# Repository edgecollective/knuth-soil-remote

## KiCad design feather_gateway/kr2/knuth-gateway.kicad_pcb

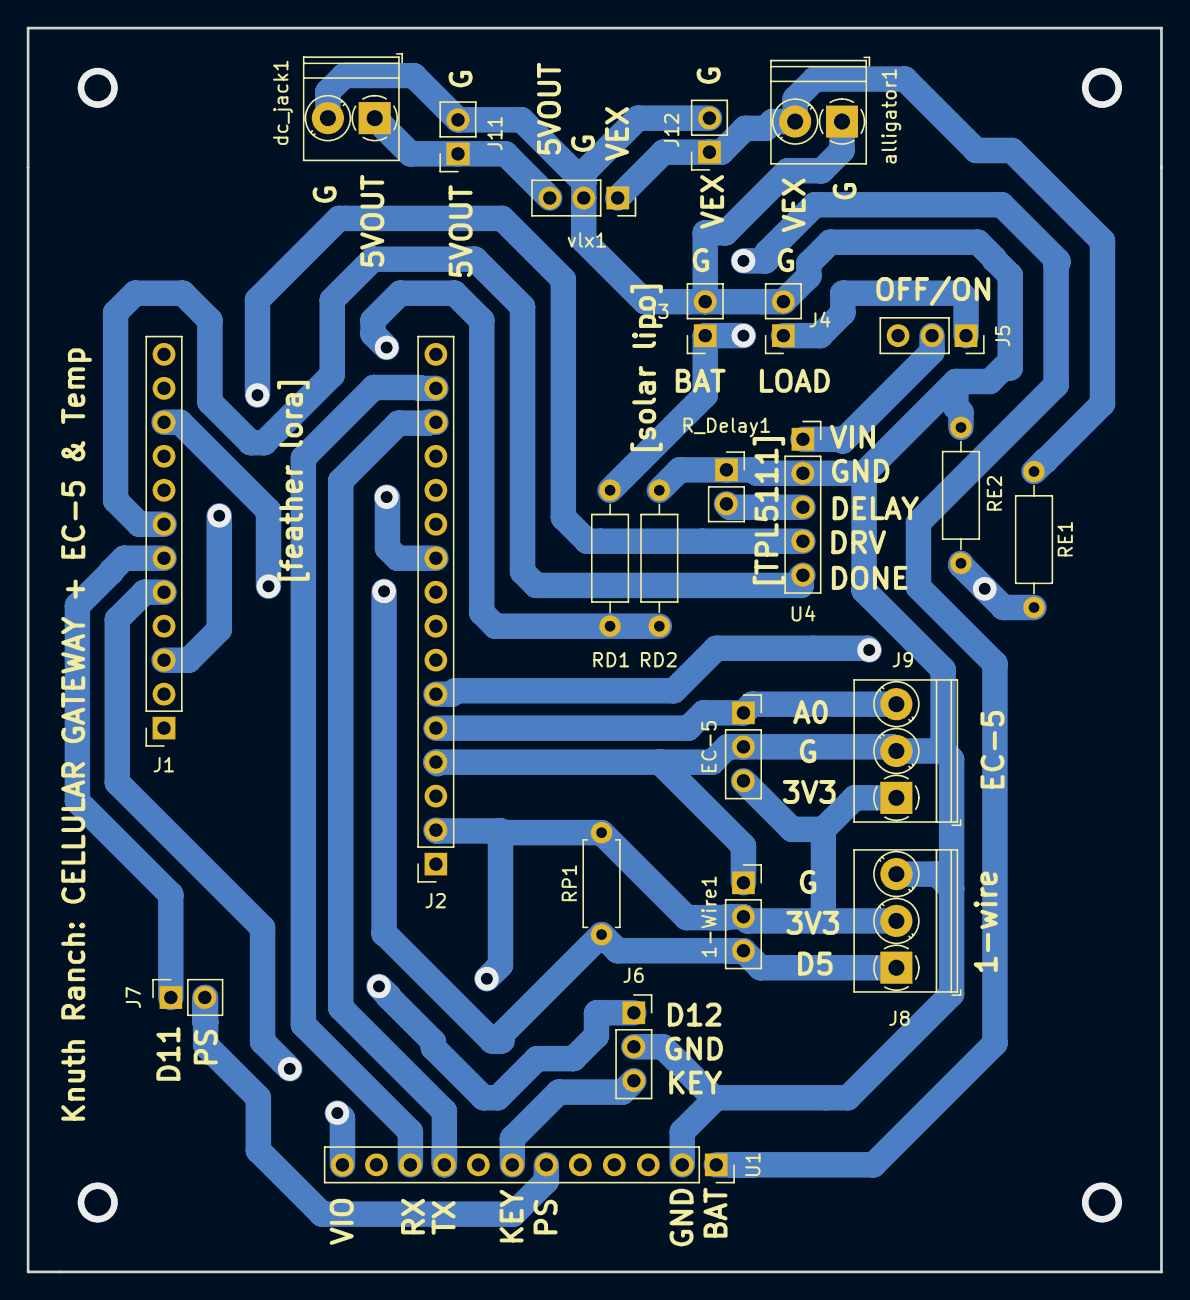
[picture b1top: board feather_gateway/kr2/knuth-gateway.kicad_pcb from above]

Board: 2 copper layers, 84.7 x 93.0 mm, 24 parts (0 on the bottom side), 20 nets.

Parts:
1-Wire1: Conn_01x03_Female; PinSocket_1x03_P2.54mm_Vertical
EC-5: Conn_01x03_Female; PinSocket_1x03_P2.54mm_Vertical
J1: FeatherLora1; PinSocket_1x12_P2.54mm_Vertical
J2: FeatherLora2; PinSocket_1x16_P2.54mm_Vertical
J3, J4, J7, J11, J12: Conn_01x02_Female; PinSocket_1x02_P2.54mm_Vertical
J5, J6: Conn_01x03_Female; PinSocket_1x03_P2.54mm_Vertical
J8, J9: Screw_Terminal_01x03; TerminalBlock_Phoenix_PT-1,5-3-3.5-H_1x03_P3.50mm_Horizontal
RD1, RD2: R; R_Axial_DIN0207_L6.3mm_D2.5mm_P10.16mm_Horizontal
RE1: R; R_Axial_DIN0207_L6.3mm_D2.5mm_P10.16mm_Horizontal
RE2: =1/14 of top R; R_Axial_DIN0207_L6.3mm_D2.5mm_P10.16mm_Horizontal
RP1: 4.7K; R_Axial_DIN0207_L6.3mm_D2.5mm_P7.62mm_Horizontal
R_Delay1: Conn_01x02_Female; PinSocket_1x02_P2.54mm_Vertical
U1: sim800; PinSocket_1x12_P2.54mm_Vertical
U4: tpl5111; PinSocket_1x05_P2.54mm_Vertical
alligator1: Screw_Terminal_01x02; TerminalBlock_Phoenix_PT-1,5-2-3.5-H_1x02_P3.50mm_Horizontal
dc_jack1: Screw_Terminal_01x02; TerminalBlock_Phoenix_PT-1,5-2-3.5-H_1x02_P3.50mm_Horizontal
vlx1: Conn_01x03_Female; PinSocket_1x03_P2.54mm_Vertical

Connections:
5V_OUT: J11.1, dc_jack1.1, vlx1.3
+3V3: 1-Wire1.2, EC-5.3, J2.2, J8.2, J9.1, RP1.2, U1.12
A0: EC-5.1, J2.5, J9.3
A1: J2.6, RE1.2, RE2.1
A5: J2.10, RD1.2, RD2.1
BATT: J3.1, RD1.1, U1.1
D5: 1-Wire1.3, J1.10, J8.1, RP1.1
D10: J1.7, U4.5
D11: J1.6, J7.1
D12: J1.5, J6.1
EXT_BAT: J12.1, RE1.1, alligator1.2, vlx1.1
FEATHER_RX: J2.14, U1.9
FEATHER_TX: J2.15, U1.10
GND: 1-Wire1.1, EC-5.2, J2.4, J3.2, J4.2, J6.2, J8.3, J9.2, J11.2, J12.2, RD2.2, RE2.2, R_Delay1.1, U1.2, U4.2, alligator1.1, dc_jack1.2, vlx1.2
KEY: J6.3, U1.7
LOAD: J4.1, J5.1
unnamed: R_Delay1.2, U4.3
PS: J7.2, U1.6
SWITCHED_LOAD: J5.2, U4.1
VBUS: J1.3, U4.4

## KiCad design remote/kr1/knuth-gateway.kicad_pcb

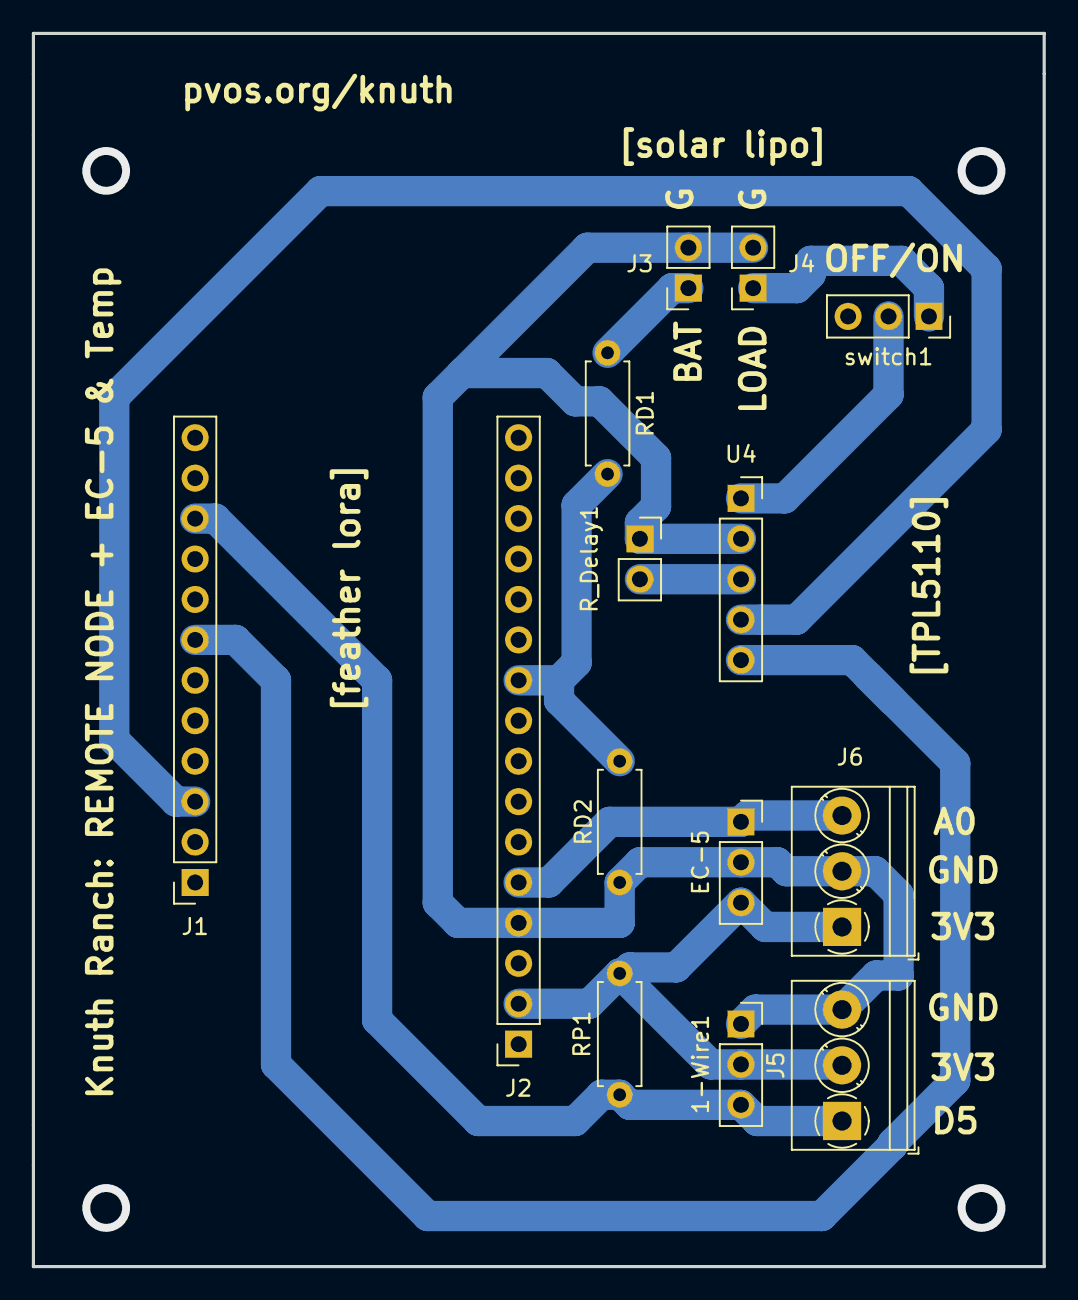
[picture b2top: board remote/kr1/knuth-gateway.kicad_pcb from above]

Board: 2 copper layers, 63.5 x 77.5 mm, 14 parts (0 on the bottom side), 11 nets.

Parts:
1-Wire1: Conn_01x03_Female; PinSocket_1x03_P2.54mm_Vertical
EC-5: Conn_01x03_Female; PinSocket_1x03_P2.54mm_Vertical
J1: FeatherLora1; PinSocket_1x12_P2.54mm_Vertical
J2: FeatherLora2; PinSocket_1x16_P2.54mm_Vertical
J3, J4: Conn_01x02_Female; PinSocket_1x02_P2.54mm_Vertical
J5, J6: Screw_Terminal_01x03; TerminalBlock_Phoenix_PT-1,5-3-3.5-H_1x03_P3.50mm_Horizontal
RD1, RD2: R; R_Axial_DIN0207_L6.3mm_D2.5mm_P7.62mm_Horizontal
RP1: 4.7K; R_Axial_DIN0207_L6.3mm_D2.5mm_P7.62mm_Horizontal
R_Delay1: Conn_01x02_Female; PinSocket_1x02_P2.54mm_Vertical
U4: tpl5111; PinSocket_1x05_P2.54mm_Vertical
switch1: Conn_01x03_Female; PinSocket_1x03_P2.54mm_Vertical

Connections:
+3V3: 1-Wire1.2, EC-5.3, J2.2, J5.2, J6.1, RP1.2
A0: EC-5.1, J2.5, J6.3
A5: J2.10, RD1.2, RD2.1
BATT: J3.1, RD1.1
D5: 1-Wire1.3, J1.10, J5.1, RP1.1
D10: J1.7, U4.5
GND: 1-Wire1.1, EC-5.2, J2.4, J3.2, J4.2, J5.3, J6.2, RD2.2, R_Delay1.1, U4.2
LOAD: J4.1, switch1.1
unnamed: R_Delay1.2, U4.3
SWITCHED_LOAD: U4.1, switch1.2
VBUS: J1.3, U4.4

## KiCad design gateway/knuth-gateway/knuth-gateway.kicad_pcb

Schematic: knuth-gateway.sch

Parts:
J1: Conn_01x16_Female; PinSocket_1x16_P2.54mm_Vertical
J_DC_6.5V+_IN1, J_DC_6V_IN1: Conn_01x02_Female; PinSocket_1x02_P2.54mm_Vertical
Q1: Q_NPN_EBC; TO-92
Q2: Q_PNP_BCE; TO-220-3_Vertical
R1, R2, R3: R; R_Axial_DIN0204_L3.6mm_D1.6mm_P5.08mm_Horizontal
R_Delay1: Conn_01x02_Female; PinSocket_1x02_P2.54mm_Vertical
U1: FONA808; PinSocket_1x16_P2.54mm_Vertical
U2: Q_RHS; PinSocket_1x16_P2.54mm_Vertical
U3: CUI_5V_SWITCHING; PinSocket_1x03_P2.54mm_Vertical
U4: tpl5110; PinSocket_1x05_P2.54mm_Vertical
U5: adasolarlipo; PinSocket_1x04_P2.54mm_Vertical
U7: powerboost_500; PinSocket_1x08_P2.54mm_Vertical

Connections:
+BATT: Q2.3, U1.2, U4.1, U5.1
GND: J1.7, J_DC_6.5V+_IN1.2, J_DC_6V_IN1.2, Q1.1 (E), R_Delay1.1, U1.3, U1.9, U2.7, U3.2, U4.2, U5.2, U5.4, U7.2
unnamed: J1.1, U2.1, U7.8
unnamed: J1.2, U2.2
unnamed: J1.3, U1.4, U2.3
unnamed: J1.4, U2.4
unnamed: J1.5, U2.5
unnamed: J1.6, U2.6
unnamed: J1.8, U2.8
unnamed: J1.9, U2.9
unnamed: J1.10, U2.10
unnamed: J1.11, U1.7, U2.11
unnamed: J1.12, U1.6, U2.12
unnamed: J1.13, U2.13, U4.5
unnamed: J1.14, U2.14
unnamed: J1.15, U2.15
unnamed: J1.16, U2.16
unnamed: J_DC_6.5V+_IN1.1, U3.1
unnamed: J_DC_6V_IN1.1, R2.2, U5.3
unnamed: Q1.2 (B), R3.1
unnamed: Q1.3 (C), R1.2
unnamed: Q2.1, R1.1
unnamed: Q2.2, U7.3
unnamed: R2.1, U3.3
unnamed: R3.2, U4.4
unnamed: R_Delay1.2, U4.3

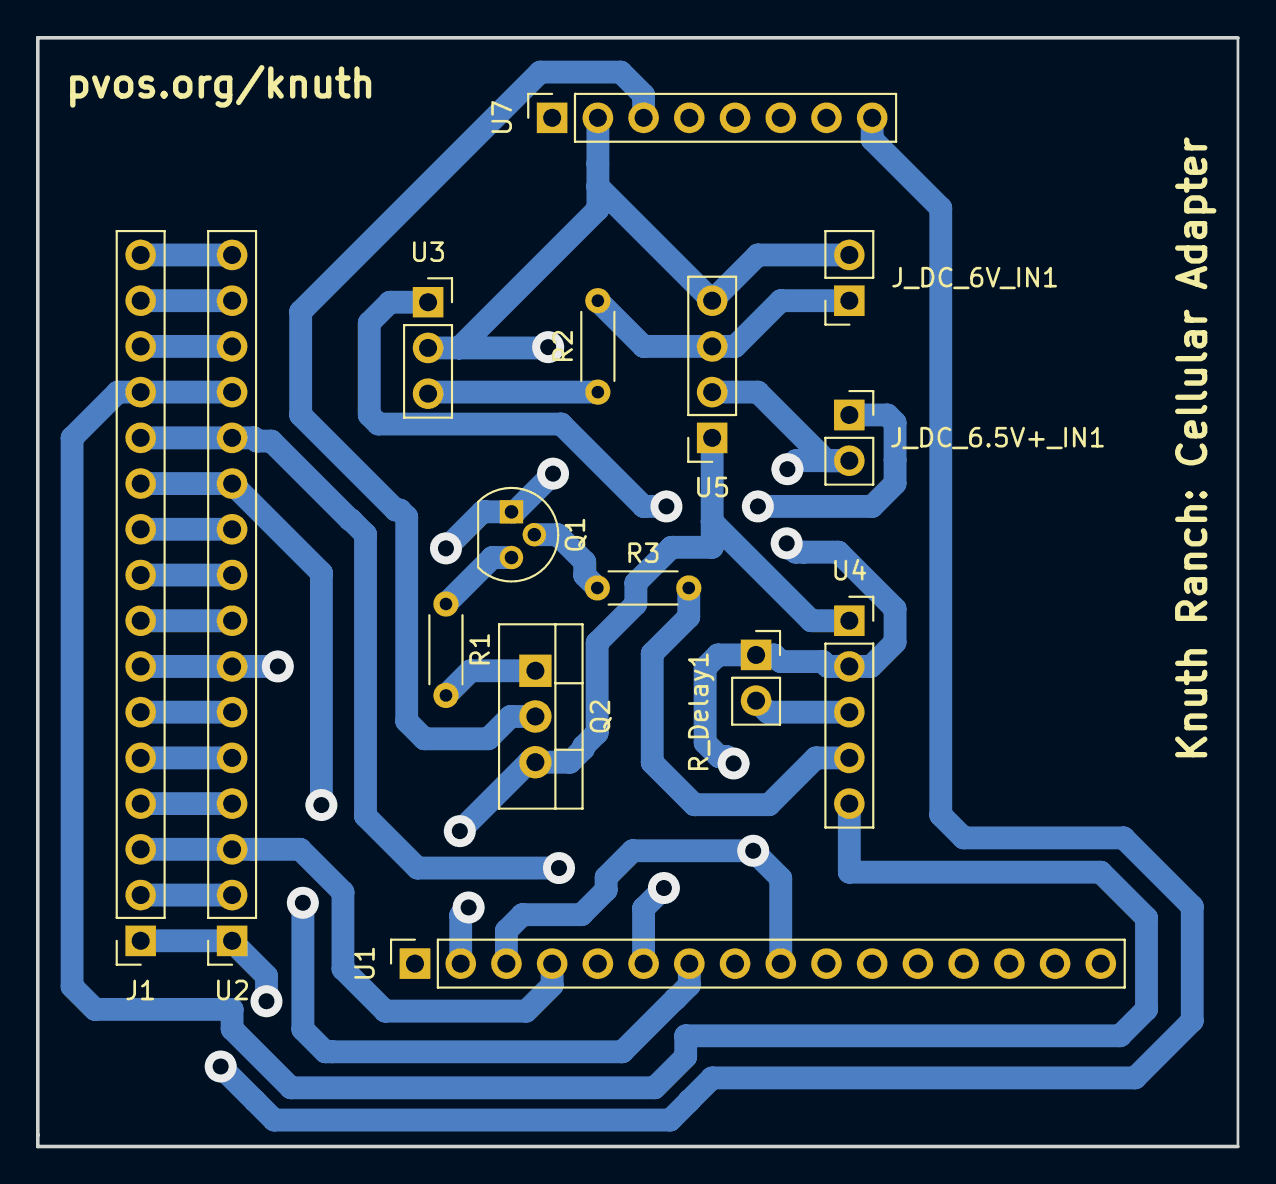
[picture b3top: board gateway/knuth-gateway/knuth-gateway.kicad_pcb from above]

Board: 2 copper layers, 66.7 x 61.6 mm, 15 parts (0 on the bottom side), 26 nets.

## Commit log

2019-07-25 wed.py is the latest good cell package!
2019-07-27 working version with one-wire and done pin; ran out of memory so dropped cell battery query
2019-07-27 fixed
